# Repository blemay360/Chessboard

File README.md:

# chessboard
Code for a chessboard with computer vision piece tracking

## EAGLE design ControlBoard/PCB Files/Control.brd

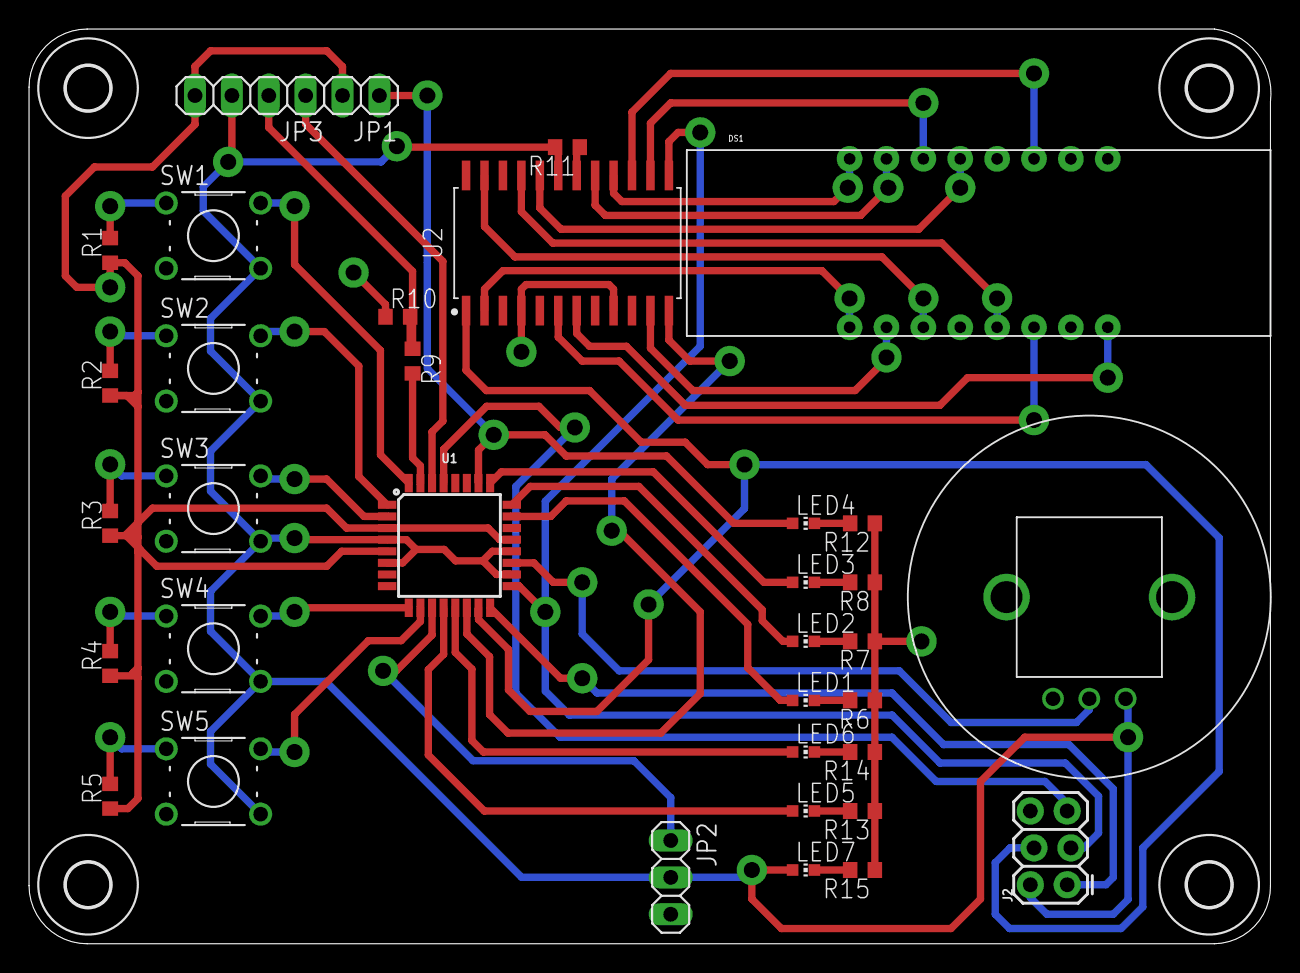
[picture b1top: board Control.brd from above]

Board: 2 copper layers, 85.5 x 63.0 mm, 39 parts (0 on the bottom side), 42 nets.

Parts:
DS1: TDCG1060M_COMMONCATHODE; TDCG1060M
J2: AVR_SPI_PROG_3X22X3_LOCK; 2X3_LOCK
JP1: 1X02
JP2: 1X03
JP3: 1X04
LED1, LED2, LED3, LED4, LED5, LED6, LED7: CHIP-LED0603
POT1: POT_PTV09A-4225F-B103
R1, R2, R3, R4, R5: 10K; R0603
R6, R7, R8, R12, R13, R14, R15: 330; R0603
R9: 3.3K; R0603
R10: 5K; R0603
R11: 33K; R0603
SW1, SW2, SW3, SW4, SW5: BUTTON; B3F-1000
U1: ATMEGA328P_TQFP; TQFP32-08
U2: MAX7219; SOIC127P1032X265-24N
U$2, U$3, U$4, U$5: 3,0

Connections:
+5V: J2.2, JP2.2, JP3.3, LED7.A, POT1.3, R11.2, SW1.3, SW1.4, SW2.3, SW2.4, SW3.3, SW3.4, SW4.3, SW4.4, SW5.3, SW5.4, U1.4, U1.6, U1.18, U1.20, U2.19
A: DS1.14, U2.14
ADC6: POT1.2, U1.19
ATMEGA_RX: JP3.1, U1.30
ATMEGA_TX: R9.2, U1.31
B: DS1.16, U2.16
C: DS1.13, U2.20
CLK: J2.3, U1.17, U2.13
CS: U1.14, U2.12
D: DS1.3, U2.23
DIG_1: DS1.1, U2.2
DIG_2: DS1.2, U2.11
DIG_3: DS1.6, U2.6
DIG_4: DS1.8, U2.7
E: DS1.5, U2.21
F: DS1.11, U2.15
G: DS1.15, U2.17
GND: J2.6, JP1.2, JP2.3, JP3.4, POT1.1, R1.1, R2.1, R3.1, R4.1, R5.1, R6.1, R7.1, R8.1, R10.1, R12.1, R13.1, R14.1, R15.1, U1.3, U1.5, U1.21, U2.4, U2.9
ISET: R11.1, U2.18
MISO: J2.1, U1.16
MOSI: J2.4, U1.15, U2.1
unnamed: LED1.C, R6.2
unnamed: LED2.C, R7.2
unnamed: LED3.C, R8.2
unnamed: LED4.C, R12.2
unnamed: LED5.C, R13.2
unnamed: LED6.C, R14.2
unnamed: LED7.C, R15.2
PB0: LED5.A, U1.12
PB1: LED6.A, U1.13
PC0: LED1.A, U1.23
PC1: LED2.A, U1.24
PC2: LED3.A, U1.25
PC3: JP1.1, LED4.A, U1.26
PD2: R1.2, SW1.1, SW1.2, U1.32
PD3: R2.2, SW2.1, SW2.2, U1.1
PD4: R3.2, SW3.1, SW3.2, U1.2
PD5: R4.2, SW4.1, SW4.2, U1.9
PD6: R5.2, SW5.1, SW5.2, U1.10
PD7: JP2.1, U1.11
PI_RX: JP3.2, R9.1, R10.2
RESET: J2.5, U1.29

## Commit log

2021-03-10 Pushing to main
2021-03-12 Finished prototype function for color identification
2021-03-13 Added support for en passant captures, pawn to queen promotions, and castling
2021-03-15 Rewrote color_array_to_uci to not be so terrible
2021-03-15 Finished updating comments
2021-03-19 Tested adding threads
2021-03-20 Switched input images to be taken from the pi camera and changed display settings to work on pi display
2021-03-20 Added flags to easier switch from running phone pictures to pi
2021-03-21 Started testing with large board
2021-03-21 Updated color detection function to use hue, still mostly untested
2021-03-21 Combined get_detection_array and get_color_array
2021-03-21 Changed display for color image
2021-03-21 Added full code for pi to support live move labeling
2021-03-21 Fixed selection for chess engine
2021-03-21 Added in code for playing computer on pi
2021-03-21 Fixed typo for right_move
2021-03-21 Fixed another typo with right_move, tested on pi. Works for a couple moves, then errors out
2021-03-22 Added testing images taken from the pi
2021-03-22 Added auto pi/laptop switching, more verbose output, and the ability to automatically stop when running from images
2021-03-22 Fixed max_file_count error for pi
2021-03-22 Added better parsing of apriltags, and code to quit if the necessary apriltags aren't found
2021-03-22 Added function to tell when edge of board is obstructed from player's arm
2021-03-25 Added histogram comparison
2021-03-25 Changed edge_clear function to use hough line transform
2021-03-25 Refined hough line transform method for measuring obstructed borders
2021-03-25 Changed threshold for hough line detection to work on pi
2021-03-26 Fixed error that crashed program when an apriltag was blocked, is mostly playable now
2021-03-27 Updated program flowchart
2021-03-27 Started testing on wooden board
2021-03-28 Started testing with better border obstruction testing
2021-03-28 Testing wooden board
2021-03-28 Fixing merge
2021-03-28 Still trying to fix merge
2021-03-28 Changed settings for hough line transform to through out short lines and be able to link across longer gaps
2021-04-01 Fixed up angle errors in edge_clear
2021-04-02 Added test program for picking a pattern out of an image
2021-04-04 Added stls for prototype construction
2021-04-04 Added testing pictures
2021-04-05 Changed border obstruction detection to work with linear celtic knot pattern
2021-04-05 Moved loading border reference image to main function
2021-04-06 Changed display variable to be global, added testing images that cause an error
2021-04-06 Fixed saving debugging images
2021-04-06 Changed margin of squares in piece detection to fix some mislabeled colors
2021-04-06 More testing images with incorrect color labeling
2021-04-06 Modified color sensing to better differentiate silver from gold
2021-04-07 Updated debugging images with apriltag error
2021-04-07 Changed how missing apriltags are treated when searching last known tag locations
2021-04-07 Fixed debugging image filenames
2021-04-07 Changed display function to be more adaptable, split main function into setup and process_game, added support for playing timestamped frames from the pi
2021-04-08 Added computer move to gui display
2021-04-08 New error found in color_array_to_uci, debugging images in this commit
2021-04-08 Changed average_color to use standard deviation instead of minimum hues
2021-04-08 Added debugging photos for an error with amounts of pieces on the board
2021-04-08 Tinkered with some values to better detect pieces
2021-04-08 Added code to remove previous debugging images when starting a game
2021-04-08 Only delete previous photos if running on pi
2021-04-11 Changed margin for edge detection of pieces and made number of pieces detected error throw out the frame
2021-04-11 Moved camera setup to setup function
2021-04-11 Made camera global variable to fix error
2021-04-11 New debugging images
2021-04-11 Added minimum radius for color measurment
2021-04-11 Added new debugging images, had problems with edge_count_threshold being set too low
2021-05-11 Added control board testing code and wrote part of the documentation report
2021-05-11 Push from pi
2021-05-11 Added footage of Scholar's Mate game
2021-05-11 Rerecorded video in original frame size
2021-05-11 Adapting Chessboard.py to work on recorded videos
2021-05-11 Added chessboard.py back
2021-05-11 Trying to rerecord again
2021-05-11 Added video back
2021-05-13 Tweaked color detection algorithm to work with current lighting and added tons of processed images for presentation
2021-05-17 Added control board PCB files and organized some folders
2021-05-19 Finished documentation report
2021-05-19 Error pictures added
2021-05-19 Added condition to discard frames where color of pieces seem to switch
2022-08-14 Started to reorganize directory layout

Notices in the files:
parts and their libraries:
SparkFun-IC-Microcontroller: Licensing: Creative Commons ShareAlike 4.0 International - https://creativecommons.org/licenses/by-sa/4.0
